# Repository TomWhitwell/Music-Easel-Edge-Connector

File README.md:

# Music Easel Edge Connector
 
 *** NB: THIS IS NOT FULLY TESTED, read below*** 
 
 This is an Eagle Library for the card edge for Buchla Music Easel expansion cards. This should work with BEMI Music Easels and clones, apart from the 208r rev1  which has different pinout. NB: I take no responsibility at all for anything designed using this part.
 
 This is just the edge connector library, and two boards showing the part in situ - neither of these board layouts will do anything. This is not a prototype board! 
 
 I've made a PCB with the minimal version, works well - put it on standard 1.6mm PCB with ENIG finish and no special edge treatment. I've checked my layout, but please carefully check for any errors as you're using it - it's not impossible that one of the traces could be incorrectly labelled. 

 There are two versions:
 
 The Full version is the whole bottom side of a standard program card. 

The Small / Minimal version is just the edge connector itself 

For both cards, take care to match the outline layer to the outline in the part - if you turn on tDocu layer, you'll see the measurements to make it easier to connect with the part 

The symbol has text explaining which pin is which: 

Things to watch out for: 
* The edge connector runs right up to the edge of the board, so you may get design rule errors, which you can probably ignore. 
* Eagle doesn't seem to understand that the outline layer in the part connects with the outline layer on the rest of the board, so it looks as if the outline layer is incomplete. However, this doesn't seem to be a real issue - the gerbers produced have a complete outline layer. 

Thank you to Marc Borri for his help with this, and for [Portabellabs](http://www.portabellabz.be/toolbox.html) for the pinout details, in the documentation for their excellent 208 Toolbox. 

This part was designed by Tom Whitwell in Herne Hill, London, in June 2021. You are free to use it however you want.

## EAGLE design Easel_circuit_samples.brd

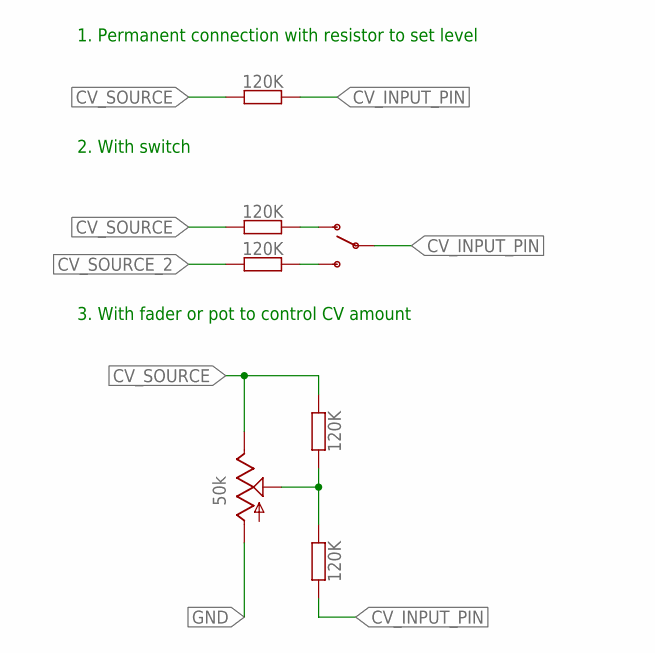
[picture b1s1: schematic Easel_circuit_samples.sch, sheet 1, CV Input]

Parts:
R1, R2, R3, R4, R5: 120K; C0603
S1: GRAYHILL_34E_SMD_TOGGLE; 34EWMSP12M6RT
VR1: 50k; 9MM_SNAP-IN_POT

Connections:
CV_INPUT_PIN: R2.1, R3.1, S1.2 (COMMON)
CV_SOURCE: R1.2, R3.2, R4.2, VR1.3 (E)
CV_SOURCE_2: R5.2
GND: VR1.1 (A); also elsewhere on the board
unnamed: R4.1, S1.1 (O)
unnamed: R1.1, R2.2, VR1.2 (S)
unnamed: R5.1, S1.3 (S)

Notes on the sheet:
3. With fader or pot to control CV amount
1. Permanent connection with resistor to set level
2. With switch

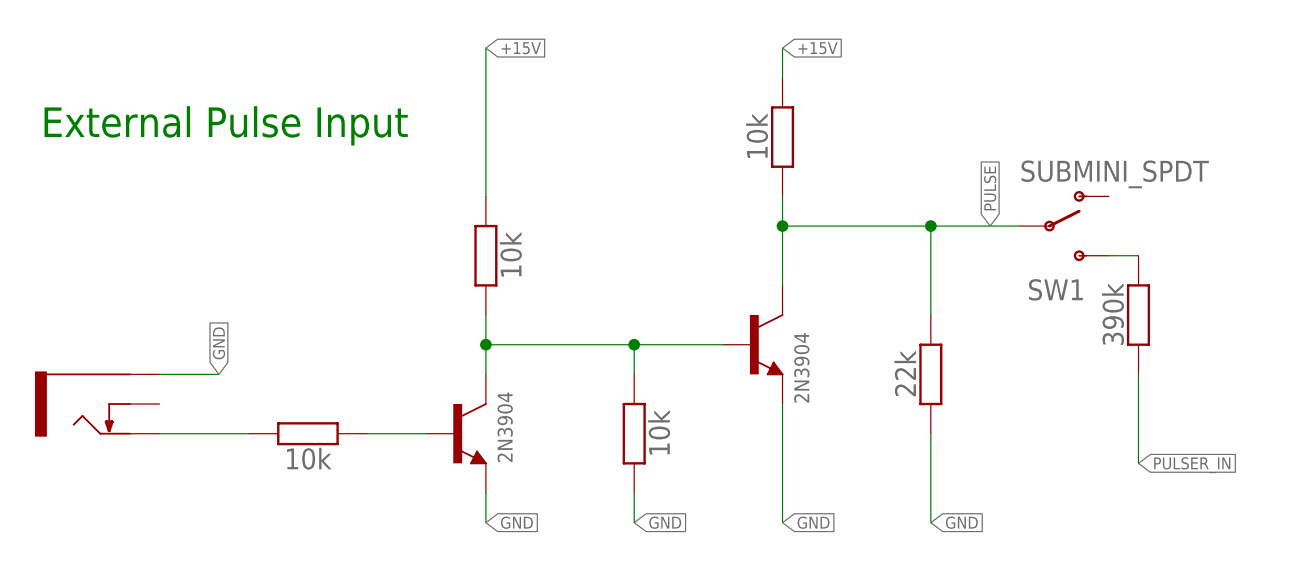
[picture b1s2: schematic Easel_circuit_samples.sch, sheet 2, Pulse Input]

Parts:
Q1: 2N3904; SC70-6
R6, R7, R8, R9: 10k; C0603
R10: 22k; C0603
R11: 390k; C0603
SW1: SUBMINI_SPDT; SUBMINI_TOGGLE
U1: THONKICONNNEW; WQP-PJ301M-12_JACK

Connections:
+15V: R7.2, R9.1
GND: Q1.1 (E), Q1.4 (E), R8.1, R10.2, U1.P$3_SLEEVE (SLEEVE); also elsewhere on the board
unnamed: R6.1, U1.P$1_TIP (TIP)
unnamed: Q1.5 (B), R6.2
unnamed: Q1.2 (B), Q1.3 (C), R7.1, R8.2
unnamed: R11.1, SW1.3 (S)
PULSE: Q1.6 (C), R9.2, R10.1, SW1.COM (COMMON)
PULSER_IN: R11.2

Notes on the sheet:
External Pulse Input

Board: 2 copper layers, 16 parts (0 on the bottom side), 12 nets, no tracks yet.

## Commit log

2021-06-27 Minor updates
2021-06-27 initial upload
2021-07-06 Straightened bottom edge on both footprints
2021-07-06 Remove solder paste from edge connector pads
2021-09-05 remove cruft
2022-01-28 Library updates
2022-02-08 Add right aligned full card edge connector
2022-02-08 fixed right aligned edge connector

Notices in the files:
parts and their libraries:
SparkFun-DiscreteSemi: Licensing: Creative Commons ShareAlike 4.0 International - https://creativecommons.org/licenses/by-sa/4.0
